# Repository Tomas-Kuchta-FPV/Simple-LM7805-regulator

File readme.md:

# Simple LM7805 regulator
It's for my school project, and why not to publish it on github.

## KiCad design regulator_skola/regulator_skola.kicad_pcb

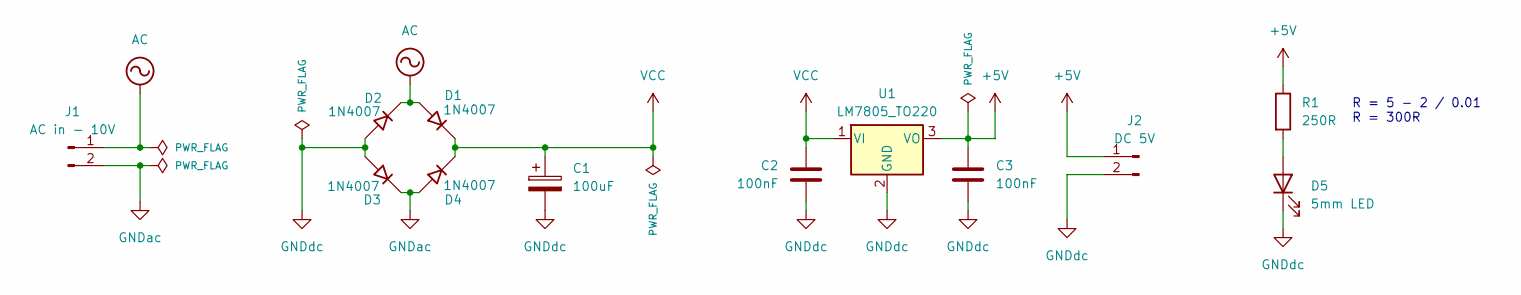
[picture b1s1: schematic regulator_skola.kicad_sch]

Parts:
C1: 100uF; CP_Radial_D6.3mm_P2.50mm
C2, C3: 100nF; C_Disc_D6.0mm_W2.5mm_P5.00mm
D1, D2, D3, D4: 1N4007; D_DO-41_SOD81_P10.16mm_Horizontal
D5: 5mm LED; LED_D5.0mm
J1: AC in - 10V; PinHeader_1x02_P2.54mm_Vertical
J2: DC 5V; PinHeader_1x02_P2.54mm_Vertical
R1: 250R; R_Axial_DIN0207_L6.3mm_D2.5mm_P7.62mm_Horizontal
U1: LM7805_TO220; TO-220-3_Vertical

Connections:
+5V: C3.1, J2.1, R1.1, U1.3 (VO)
AC: D1.2 (A), D2.1 (K), J1.1
GNDac: D3.1 (K), D4.2 (A), J1.2
GNDdc: C1.2, C2.2, C3.2, D2.2 (A), D3.2 (A), D5.1 (K), J2.2, U1.2 (GND)
unnamed: D5.2 (A), R1.2
VCC: C1.1, C2.1, D1.1 (K), D4.1 (K), U1.1 (VI)

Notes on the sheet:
R = 5 - 2 / 0.01 R = 300R

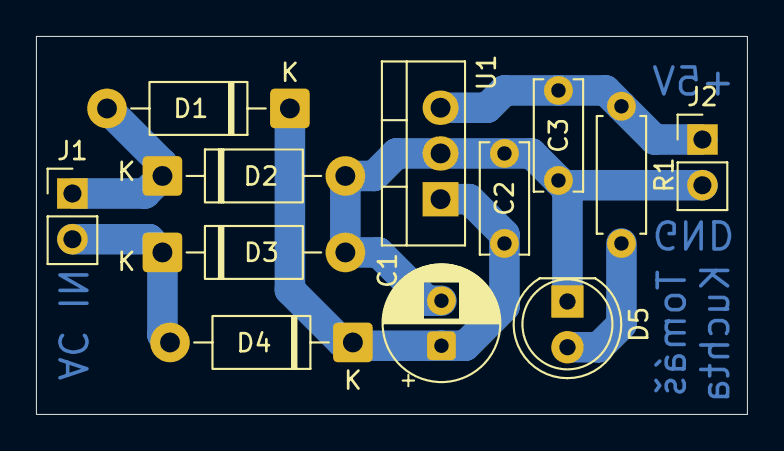
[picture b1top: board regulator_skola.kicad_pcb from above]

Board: 2 copper layers, 39.5 x 21.0 mm, 12 parts (0 on the bottom side), 6 nets.

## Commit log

2026-02-06 Add the project files
2026-02-13 Finishing touches
2026-02-13 add readme
2026-02-13 modify .gitignore
